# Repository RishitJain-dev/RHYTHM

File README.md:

# RHYTHM
a grid of 168 RGB LEDs to connect with hackatime or github to represent your coding time in real life, all controlled by a XIAO ESP32-S3 and LiPo battery

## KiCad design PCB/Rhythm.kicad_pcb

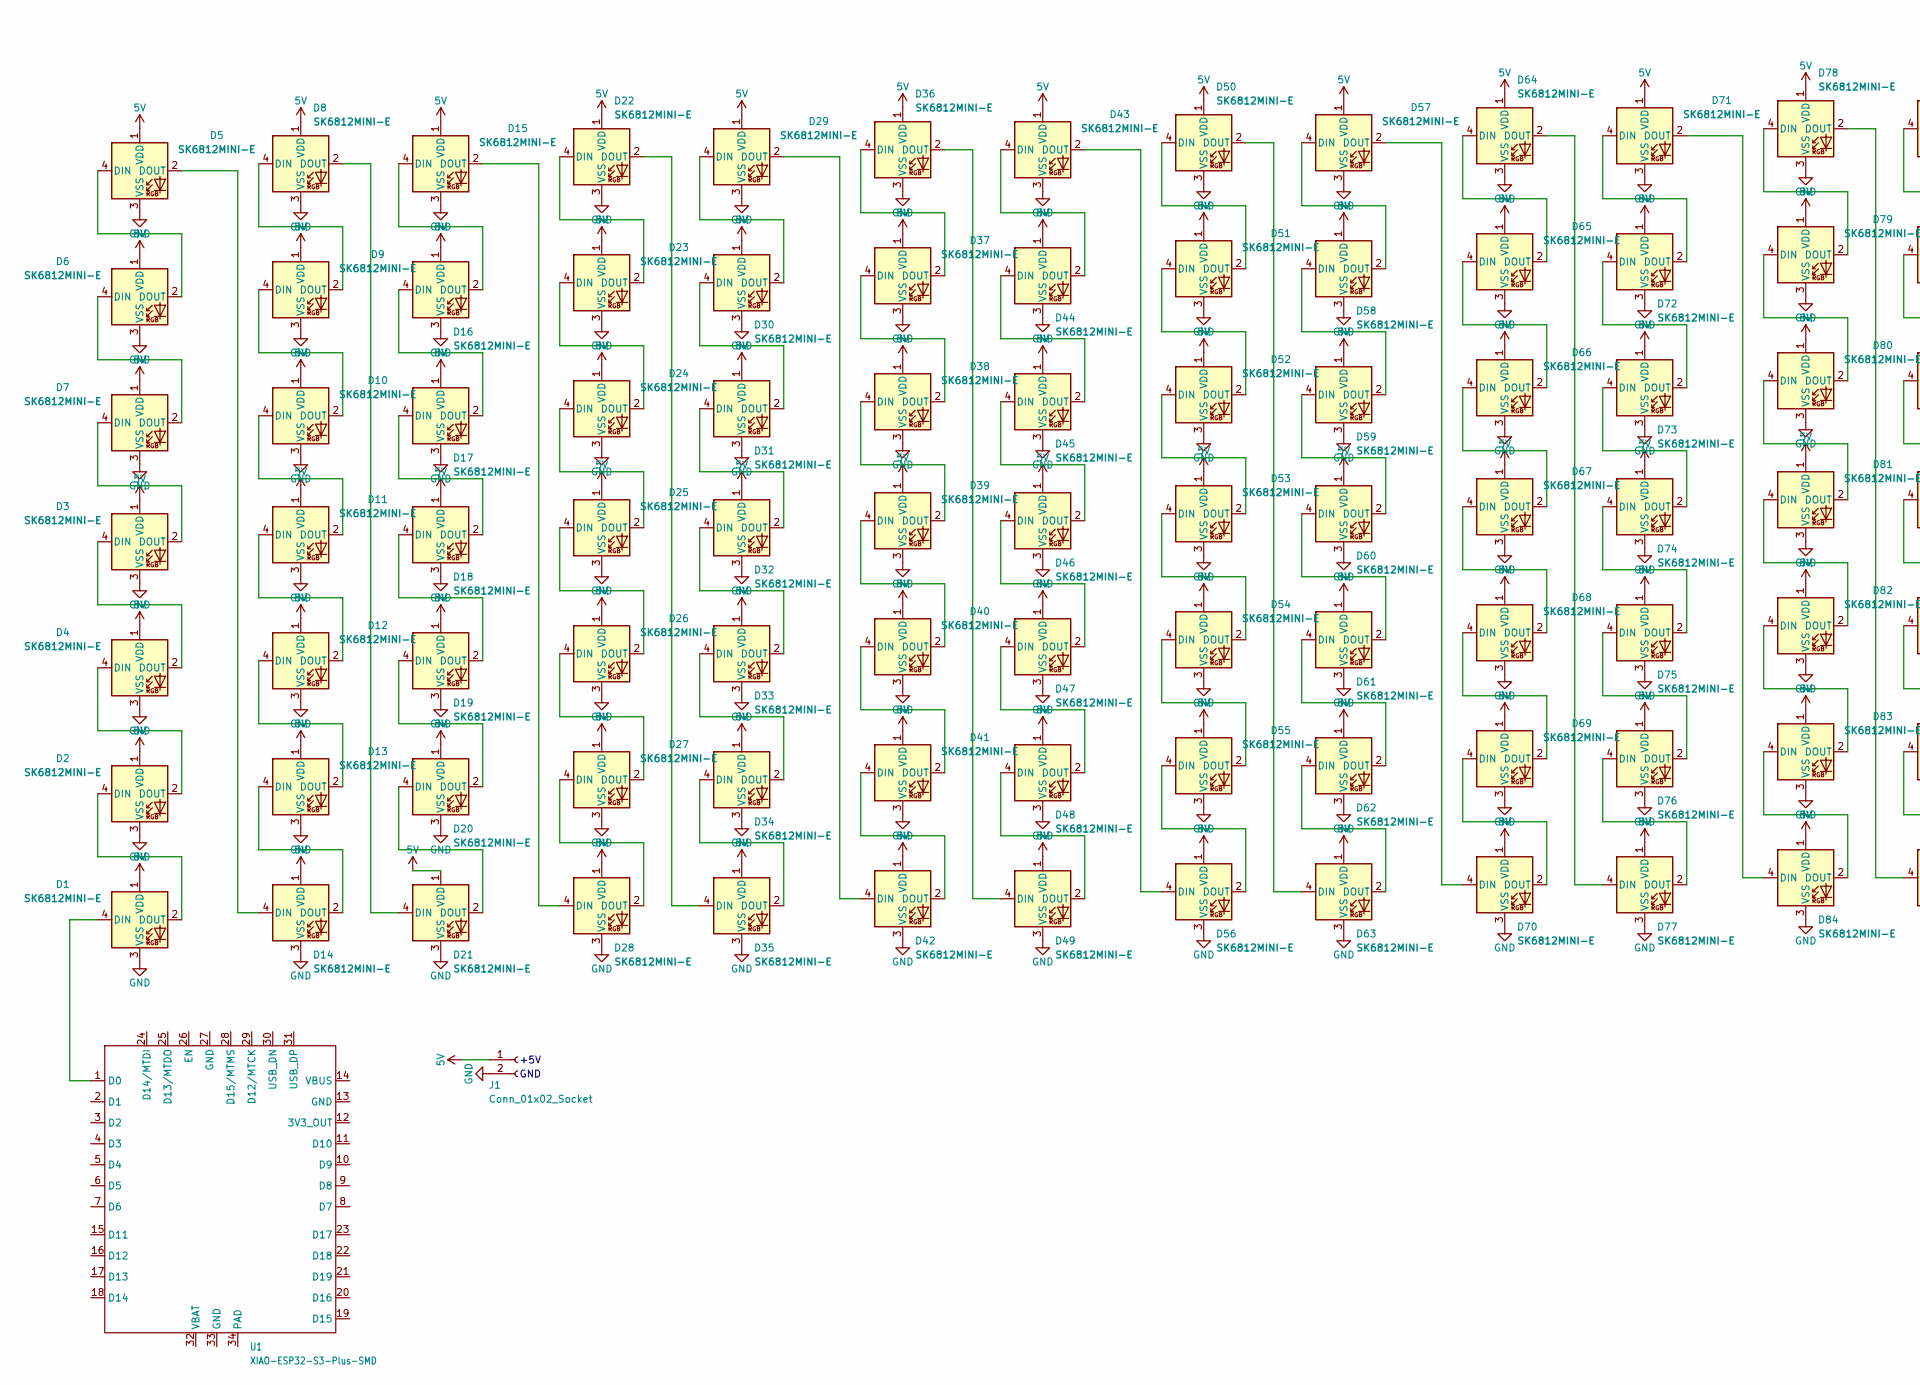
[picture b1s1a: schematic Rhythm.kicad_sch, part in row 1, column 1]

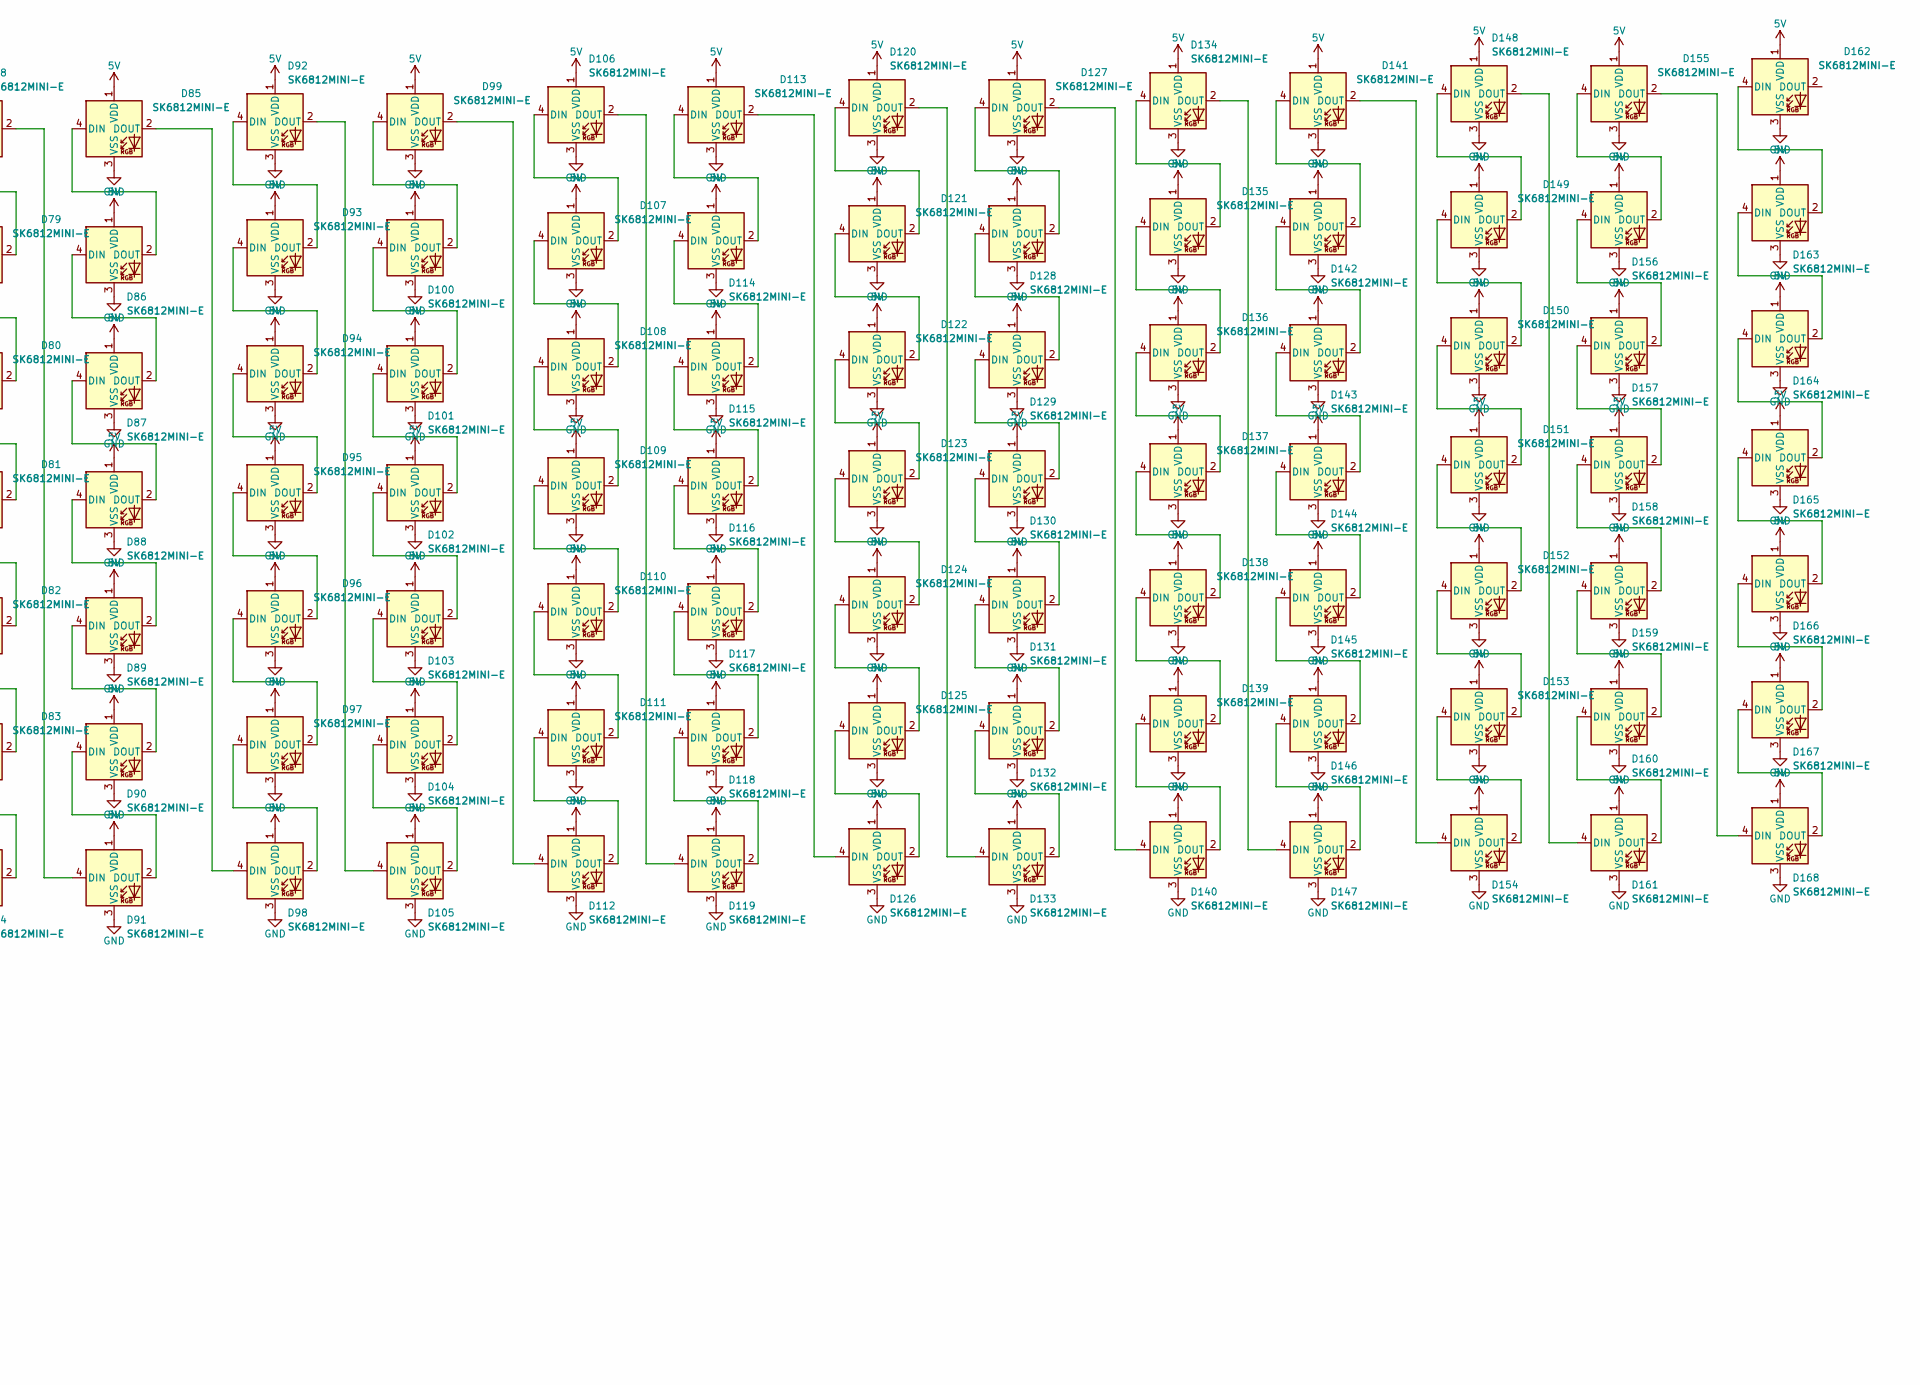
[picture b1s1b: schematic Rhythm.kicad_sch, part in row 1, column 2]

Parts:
D1, D2, D3, D4, D5, D6, D7, D8, D9, D10, D11, D12, D13, D14, D15, D16, D17, D18, D19, D20, D21, D22, D23, D24, D25, D26, D27, D28, D29, D30, D31, D32, D33, D34, D35, D36, D37, D38, D39, D40, D41, D42, D43, D44, D45, D46, D47, D48, D49, D50, D51, D52, D53, D54, D55, D56, D57, D58, D59, D60, D61, D62, D63, D64, D65, D66, D67, D68, D69, D70, D71, D72, D73, D74, D75, D76, D77, D78, D79, D80, D81, D82, D83, D84, D85, D86, D87, D88, D89, D90, D91, D92, D93, D94, D95, D96, D97, D98, D99, D100, D101, D102, D103, D104, D105, D106, D107, D108, D109, D110, D111, D112, D113, D114, D115, D116, D117, D118, D119, D120, D121, D122, D123, D124, D125, D126, D127, D128, D129, D130, D131, D132, D133, D134, D135, D136, D137, D138, D139, D140, D141, D142, D143, D144, D145, D146, D147, D148, D149, D150, D151, D152, D153, D154, D155, D156, D157, D158, D159, D160, D161, D162, D163, D164, D165, D166, D167, D168: SK6812MINI-E; SK6812MINI-E_fixed
J1: Conn_01x02_Socket; JST_EH_B2B-EH-A_1x02_P2.50mm_Vertical
U1: XIAO-ESP32-S3-Plus-SMD

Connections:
5V: D1.1 (VDD), D2.1 (VDD), D3.1 (VDD), D4.1 (VDD), D5.1 (VDD), D6.1 (VDD), D7.1 (VDD), D8.1 (VDD), D9.1 (VDD), D10.1 (VDD), D11.1 (VDD), D12.1 (VDD), D13.1 (VDD), D14.1 (VDD), D15.1 (VDD), D16.1 (VDD), D17.1 (VDD), D18.1 (VDD), D19.1 (VDD), D20.1 (VDD), D21.1 (VDD), D22.1 (VDD), D23.1 (VDD), D24.1 (VDD), D25.1 (VDD), D26.1 (VDD), D27.1 (VDD), D28.1 (VDD), D29.1 (VDD), D30.1 (VDD), D31.1 (VDD), D32.1 (VDD), D33.1 (VDD), D34.1 (VDD), D35.1 (VDD), D36.1 (VDD), D37.1 (VDD), D38.1 (VDD), D39.1 (VDD), D40.1 (VDD), D41.1 (VDD), D42.1 (VDD), D43.1 (VDD), D44.1 (VDD), D45.1 (VDD), D46.1 (VDD), D47.1 (VDD), D48.1 (VDD), D49.1 (VDD), D50.1 (VDD), D51.1 (VDD), D52.1 (VDD), D53.1 (VDD), D54.1 (VDD), D55.1 (VDD), D56.1 (VDD), D57.1 (VDD), D58.1 (VDD), D59.1 (VDD), D60.1 (VDD), D61.1 (VDD), D62.1 (VDD), D63.1 (VDD), D64.1 (VDD), D65.1 (VDD), D66.1 (VDD), D67.1 (VDD), D68.1 (VDD), D69.1 (VDD), D70.1 (VDD), D71.1 (VDD), D72.1 (VDD), D73.1 (VDD), D74.1 (VDD), D75.1 (VDD), D76.1 (VDD), D77.1 (VDD), D78.1 (VDD), D79.1 (VDD), D80.1 (VDD), D81.1 (VDD), D82.1 (VDD), D83.1 (VDD), D84.1 (VDD), D85.1 (VDD), D86.1 (VDD), D87.1 (VDD), D88.1 (VDD), D89.1 (VDD), D90.1 (VDD), D91.1 (VDD), D92.1 (VDD), D93.1 (VDD), D94.1 (VDD), D95.1 (VDD), D96.1 (VDD), D97.1 (VDD), D98.1 (VDD), D99.1 (VDD), D100.1 (VDD), D101.1 (VDD), D102.1 (VDD), D103.1 (VDD), D104.1 (VDD), D105.1 (VDD), D106.1 (VDD), D107.1 (VDD), D108.1 (VDD), D109.1 (VDD), D110.1 (VDD), D111.1 (VDD), D112.1 (VDD), D113.1 (VDD), D114.1 (VDD), D115.1 (VDD), D116.1 (VDD), D117.1 (VDD), D118.1 (VDD), D119.1 (VDD), D120.1 (VDD), D121.1 (VDD), D122.1 (VDD), D123.1 (VDD), D124.1 (VDD), D125.1 (VDD), D126.1 (VDD), D127.1 (VDD), D128.1 (VDD), D129.1 (VDD), D130.1 (VDD), D131.1 (VDD), D132.1 (VDD), D133.1 (VDD), D134.1 (VDD), D135.1 (VDD), D136.1 (VDD), D137.1 (VDD), D138.1 (VDD), D139.1 (VDD), D140.1 (VDD), D141.1 (VDD), D142.1 (VDD), D143.1 (VDD), D144.1 (VDD), D145.1 (VDD), D146.1 (VDD), D147.1 (VDD), D148.1 (VDD), D149.1 (VDD), D150.1 (VDD), D151.1 (VDD), D152.1 (VDD), D153.1 (VDD), D154.1 (VDD), D155.1 (VDD), D156.1 (VDD), D157.1 (VDD), D158.1 (VDD), D159.1 (VDD), D160.1 (VDD), D161.1 (VDD), D162.1 (VDD), D163.1 (VDD), D164.1 (VDD), D165.1 (VDD), D166.1 (VDD), D167.1 (VDD), D168.1 (VDD), J1.1
GND: D1.3 (VSS), D2.3 (VSS), D3.3 (VSS), D4.3 (VSS), D5.3 (VSS), D6.3 (VSS), D7.3 (VSS), D8.3 (VSS), D9.3 (VSS), D10.3 (VSS), D11.3 (VSS), D12.3 (VSS), D13.3 (VSS), D14.3 (VSS), D15.3 (VSS), D16.3 (VSS), D17.3 (VSS), D18.3 (VSS), D19.3 (VSS), D20.3 (VSS), D21.3 (VSS), D22.3 (VSS), D23.3 (VSS), D24.3 (VSS), D25.3 (VSS), D26.3 (VSS), D27.3 (VSS), D28.3 (VSS), D29.3 (VSS), D30.3 (VSS), D31.3 (VSS), D32.3 (VSS), D33.3 (VSS), D34.3 (VSS), D35.3 (VSS), D36.3 (VSS), D37.3 (VSS), D38.3 (VSS), D39.3 (VSS), D40.3 (VSS), D41.3 (VSS), D42.3 (VSS), D43.3 (VSS), D44.3 (VSS), D45.3 (VSS), D46.3 (VSS), D47.3 (VSS), D48.3 (VSS), D49.3 (VSS), D50.3 (VSS), D51.3 (VSS), D52.3 (VSS), D53.3 (VSS), D54.3 (VSS), D55.3 (VSS), D56.3 (VSS), D57.3 (VSS), D58.3 (VSS), D59.3 (VSS), D60.3 (VSS), D61.3 (VSS), D62.3 (VSS), D63.3 (VSS), D64.3 (VSS), D65.3 (VSS), D66.3 (VSS), D67.3 (VSS), D68.3 (VSS), D69.3 (VSS), D70.3 (VSS), D71.3 (VSS), D72.3 (VSS), D73.3 (VSS), D74.3 (VSS), D75.3 (VSS), D76.3 (VSS), D77.3 (VSS), D78.3 (VSS), D79.3 (VSS), D80.3 (VSS), D81.3 (VSS), D82.3 (VSS), D83.3 (VSS), D84.3 (VSS), D85.3 (VSS), D86.3 (VSS), D87.3 (VSS), D88.3 (VSS), D89.3 (VSS), D90.3 (VSS), D91.3 (VSS), D92.3 (VSS), D93.3 (VSS), D94.3 (VSS), D95.3 (VSS), D96.3 (VSS), D97.3 (VSS), D98.3 (VSS), D99.3 (VSS), D100.3 (VSS), D101.3 (VSS), D102.3 (VSS), D103.3 (VSS), D104.3 (VSS), D105.3 (VSS), D106.3 (VSS), D107.3 (VSS), D108.3 (VSS), D109.3 (VSS), D110.3 (VSS), D111.3 (VSS), D112.3 (VSS), D113.3 (VSS), D114.3 (VSS), D115.3 (VSS), D116.3 (VSS), D117.3 (VSS), D118.3 (VSS), D119.3 (VSS), D120.3 (VSS), D121.3 (VSS), D122.3 (VSS), D123.3 (VSS), D124.3 (VSS), D125.3 (VSS), D126.3 (VSS), D127.3 (VSS), D128.3 (VSS), D129.3 (VSS), D130.3 (VSS), D131.3 (VSS), D132.3 (VSS), D133.3 (VSS), D134.3 (VSS), D135.3 (VSS), D136.3 (VSS), D137.3 (VSS), D138.3 (VSS), D139.3 (VSS), D140.3 (VSS), D141.3 (VSS), D142.3 (VSS), D143.3 (VSS), D144.3 (VSS), D145.3 (VSS), D146.3 (VSS), D147.3 (VSS), D148.3 (VSS), D149.3 (VSS), D150.3 (VSS), D151.3 (VSS), D152.3 (VSS), D153.3 (VSS), D154.3 (VSS), D155.3 (VSS), D156.3 (VSS), D157.3 (VSS), D158.3 (VSS), D159.3 (VSS), D160.3 (VSS), D161.3 (VSS), D162.3 (VSS), D163.3 (VSS), D164.3 (VSS), D165.3 (VSS), D166.3 (VSS), D167.3 (VSS), D168.3 (VSS), J1.2
unnamed: D1.4 (DIN), U1.1 (D0_1)
unnamed: D1.2 (DOUT), D2.4 (DIN)
unnamed: D2.2 (DOUT), D4.4 (DIN)
unnamed: D3.4 (DIN), D4.2 (DOUT)
unnamed: D3.2 (DOUT), D7.4 (DIN)
unnamed: D5.4 (DIN), D6.2 (DOUT)
unnamed: D6.4 (DIN), D7.2 (DOUT)
unnamed: D8.4 (DIN), D9.2 (DOUT)
unnamed: D10.4 (DIN), D11.2 (DOUT)
unnamed: D9.4 (DIN), D10.2 (DOUT)
unnamed: D11.4 (DIN), D12.2 (DOUT)
unnamed: D12.4 (DIN), D13.2 (DOUT)
unnamed: D13.4 (DIN), D14.2 (DOUT)
unnamed: D5.2 (DOUT), D14.4 (DIN)
unnamed: D15.4 (DIN), D16.2 (DOUT)
unnamed: D15.2 (DOUT), D28.4 (DIN)
unnamed: D16.4 (DIN), D17.2 (DOUT)
unnamed: D17.4 (DIN), D18.2 (DOUT)
unnamed: D18.4 (DIN), D19.2 (DOUT)
unnamed: D19.4 (DIN), D20.2 (DOUT)
unnamed: D20.4 (DIN), D21.2 (DOUT)
unnamed: D8.2 (DOUT), D21.4 (DIN)
unnamed: D22.4 (DIN), D23.2 (DOUT)
unnamed: D22.2 (DOUT), D35.4 (DIN)
unnamed: D23.4 (DIN), D24.2 (DOUT)
unnamed: D24.4 (DIN), D25.2 (DOUT)
unnamed: D25.4 (DIN), D26.2 (DOUT)
unnamed: D26.4 (DIN), D27.2 (DOUT)
unnamed: D27.4 (DIN), D28.2 (DOUT)
unnamed: D29.4 (DIN), D30.2 (DOUT)
unnamed: D29.2 (DOUT), D42.4 (DIN)
unnamed: D30.4 (DIN), D31.2 (DOUT)
unnamed: D31.4 (DIN), D32.2 (DOUT)
unnamed: D32.4 (DIN), D33.2 (DOUT)
unnamed: D33.4 (DIN), D34.2 (DOUT)
unnamed: D34.4 (DIN), D35.2 (DOUT)
unnamed: D36.4 (DIN), D37.2 (DOUT)
unnamed: D36.2 (DOUT), D49.4 (DIN)
unnamed: D37.4 (DIN), D38.2 (DOUT)
unnamed: D38.4 (DIN), D39.2 (DOUT)
unnamed: D39.4 (DIN), D40.2 (DOUT)
unnamed: D40.4 (DIN), D41.2 (DOUT)
unnamed: D41.4 (DIN), D42.2 (DOUT)
unnamed: D43.4 (DIN), D44.2 (DOUT)
unnamed: D43.2 (DOUT), D56.4 (DIN)
unnamed: D44.4 (DIN), D45.2 (DOUT)
unnamed: D45.4 (DIN), D46.2 (DOUT)
unnamed: D46.4 (DIN), D47.2 (DOUT)
unnamed: D47.4 (DIN), D48.2 (DOUT)
unnamed: D48.4 (DIN), D49.2 (DOUT)
unnamed: D50.4 (DIN), D51.2 (DOUT)
unnamed: D50.2 (DOUT), D63.4 (DIN)
unnamed: D51.4 (DIN), D52.2 (DOUT)
unnamed: D52.4 (DIN), D53.2 (DOUT)
unnamed: D53.4 (DIN), D54.2 (DOUT)
unnamed: D54.4 (DIN), D55.2 (DOUT)
unnamed: D55.4 (DIN), D56.2 (DOUT)
unnamed: D57.4 (DIN), D58.2 (DOUT)
unnamed: D57.2 (DOUT), D70.4 (DIN)
unnamed: D58.4 (DIN), D59.2 (DOUT)
unnamed: D59.4 (DIN), D60.2 (DOUT)
unnamed: D60.4 (DIN), D61.2 (DOUT)
unnamed: D61.4 (DIN), D62.2 (DOUT)
unnamed: D62.4 (DIN), D63.2 (DOUT)
unnamed: D64.4 (DIN), D65.2 (DOUT)
unnamed: D64.2 (DOUT), D77.4 (DIN)
unnamed: D65.4 (DIN), D66.2 (DOUT)
unnamed: D66.4 (DIN), D67.2 (DOUT)
unnamed: D67.4 (DIN), D68.2 (DOUT)
unnamed: D68.4 (DIN), D69.2 (DOUT)
unnamed: D69.4 (DIN), D70.2 (DOUT)
unnamed: D71.4 (DIN), D72.2 (DOUT)
unnamed: D71.2 (DOUT), D84.4 (DIN)
unnamed: D72.4 (DIN), D73.2 (DOUT)
unnamed: D73.4 (DIN), D74.2 (DOUT)
unnamed: D74.4 (DIN), D75.2 (DOUT)
unnamed: D75.4 (DIN), D76.2 (DOUT)
unnamed: D76.4 (DIN), D77.2 (DOUT)
unnamed: D78.4 (DIN), D79.2 (DOUT)
unnamed: D78.2 (DOUT), D91.4 (DIN)
unnamed: D79.4 (DIN), D80.2 (DOUT)
unnamed: D80.4 (DIN), D81.2 (DOUT)
unnamed: D81.4 (DIN), D82.2 (DOUT)
unnamed: D82.4 (DIN), D83.2 (DOUT)
unnamed: D83.4 (DIN), D84.2 (DOUT)
unnamed: D85.4 (DIN), D86.2 (DOUT)
unnamed: D85.2 (DOUT), D98.4 (DIN)
unnamed: D86.4 (DIN), D87.2 (DOUT)
unnamed: D87.4 (DIN), D88.2 (DOUT)
unnamed: D88.4 (DIN), D89.2 (DOUT)
unnamed: D89.4 (DIN), D90.2 (DOUT)
unnamed: D90.4 (DIN), D91.2 (DOUT)
unnamed: D92.4 (DIN), D93.2 (DOUT)
unnamed: D93.4 (DIN), D94.2 (DOUT)
unnamed: D94.4 (DIN), D95.2 (DOUT)
unnamed: D95.4 (DIN), D96.2 (DOUT)
unnamed: D96.4 (DIN), D97.2 (DOUT)
unnamed: D97.4 (DIN), D98.2 (DOUT)
unnamed: D100.4 (DIN), D101.2 (DOUT)
unnamed: D99.4 (DIN), D100.2 (DOUT)
unnamed: D101.4 (DIN), D102.2 (DOUT)
unnamed: D102.4 (DIN), D103.2 (DOUT)
unnamed: D103.4 (DIN), D104.2 (DOUT)
unnamed: D104.4 (DIN), D105.2 (DOUT)
unnamed: D92.2 (DOUT), D105.4 (DIN)
unnamed: D106.4 (DIN), D107.2 (DOUT)
unnamed: D106.2 (DOUT), D119.4 (DIN)
unnamed: D107.4 (DIN), D108.2 (DOUT)
unnamed: D108.4 (DIN), D109.2 (DOUT)
unnamed: D109.4 (DIN), D110.2 (DOUT)
unnamed: D110.4 (DIN), D111.2 (DOUT)
unnamed: D111.4 (DIN), D112.2 (DOUT)
unnamed: D99.2 (DOUT), D112.4 (DIN)
unnamed: D113.4 (DIN), D114.2 (DOUT)
unnamed: D113.2 (DOUT), D126.4 (DIN)
unnamed: D114.4 (DIN), D115.2 (DOUT)
unnamed: D115.4 (DIN), D116.2 (DOUT)
unnamed: D116.4 (DIN), D117.2 (DOUT)
unnamed: D117.4 (DIN), D118.2 (DOUT)
unnamed: D118.4 (DIN), D119.2 (DOUT)
unnamed: D120.4 (DIN), D121.2 (DOUT)
unnamed: D120.2 (DOUT), D133.4 (DIN)
unnamed: D121.4 (DIN), D122.2 (DOUT)
unnamed: D122.4 (DIN), D123.2 (DOUT)
unnamed: D123.4 (DIN), D124.2 (DOUT)
unnamed: D124.4 (DIN), D125.2 (DOUT)
unnamed: D125.4 (DIN), D126.2 (DOUT)
unnamed: D127.4 (DIN), D128.2 (DOUT)
unnamed: D127.2 (DOUT), D140.4 (DIN)
unnamed: D128.4 (DIN), D129.2 (DOUT)
unnamed: D129.4 (DIN), D130.2 (DOUT)
unnamed: D130.4 (DIN), D131.2 (DOUT)
unnamed: D131.4 (DIN), D132.2 (DOUT)
unnamed: D132.4 (DIN), D133.2 (DOUT)
unnamed: D134.4 (DIN), D135.2 (DOUT)
unnamed: D134.2 (DOUT), D147.4 (DIN)
unnamed: D135.4 (DIN), D136.2 (DOUT)
unnamed: D136.4 (DIN), D137.2 (DOUT)
unnamed: D137.4 (DIN), D138.2 (DOUT)
unnamed: D138.4 (DIN), D139.2 (DOUT)
unnamed: D139.4 (DIN), D140.2 (DOUT)
unnamed: D141.4 (DIN), D142.2 (DOUT)
unnamed: D141.2 (DOUT), D154.4 (DIN)
unnamed: D142.4 (DIN), D143.2 (DOUT)
unnamed: D143.4 (DIN), D144.2 (DOUT)
unnamed: D144.4 (DIN), D145.2 (DOUT)
unnamed: D145.4 (DIN), D146.2 (DOUT)
unnamed: D146.4 (DIN), D147.2 (DOUT)
unnamed: D148.4 (DIN), D149.2 (DOUT)
unnamed: D148.2 (DOUT), D161.4 (DIN)
unnamed: D149.4 (DIN), D150.2 (DOUT)
unnamed: D150.4 (DIN), D151.2 (DOUT)
unnamed: D151.4 (DIN), D152.2 (DOUT)
unnamed: D152.4 (DIN), D153.2 (DOUT)
unnamed: D153.4 (DIN), D154.2 (DOUT)
unnamed: D155.4 (DIN), D156.2 (DOUT)
unnamed: D155.2 (DOUT), D168.4 (DIN)
unnamed: D156.4 (DIN), D157.2 (DOUT)
unnamed: D157.4 (DIN), D158.2 (DOUT)
unnamed: D158.4 (DIN), D159.2 (DOUT)
unnamed: D159.4 (DIN), D160.2 (DOUT)
unnamed: D160.4 (DIN), D161.2 (DOUT)
unnamed: D162.4 (DIN), D163.2 (DOUT)
unnamed: D163.4 (DIN), D164.2 (DOUT)
unnamed: D164.4 (DIN), D165.2 (DOUT)
unnamed: D165.4 (DIN), D166.2 (DOUT)
unnamed: D166.4 (DIN), D167.2 (DOUT)
unnamed: D167.4 (DIN), D168.2 (DOUT)

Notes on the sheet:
GND
+5V

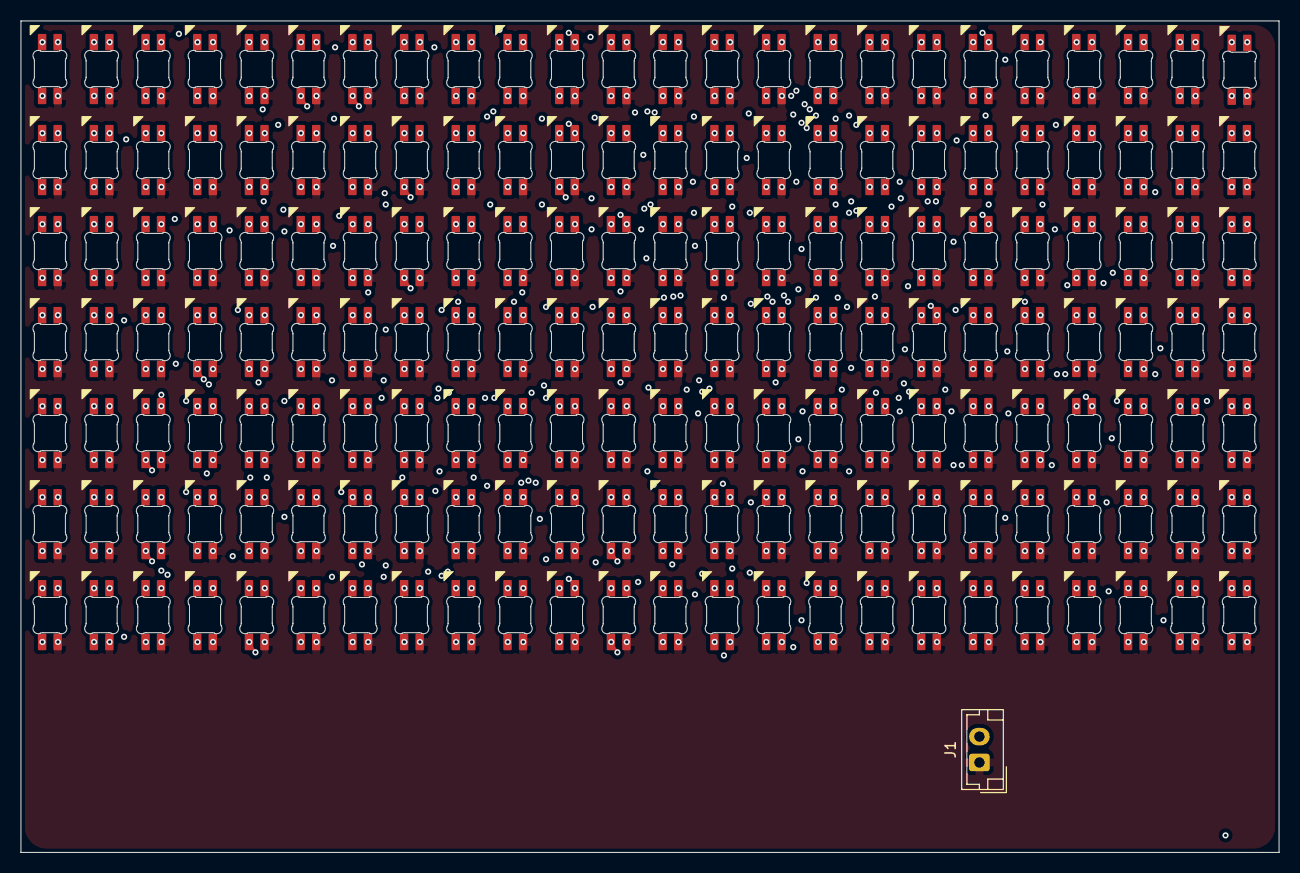
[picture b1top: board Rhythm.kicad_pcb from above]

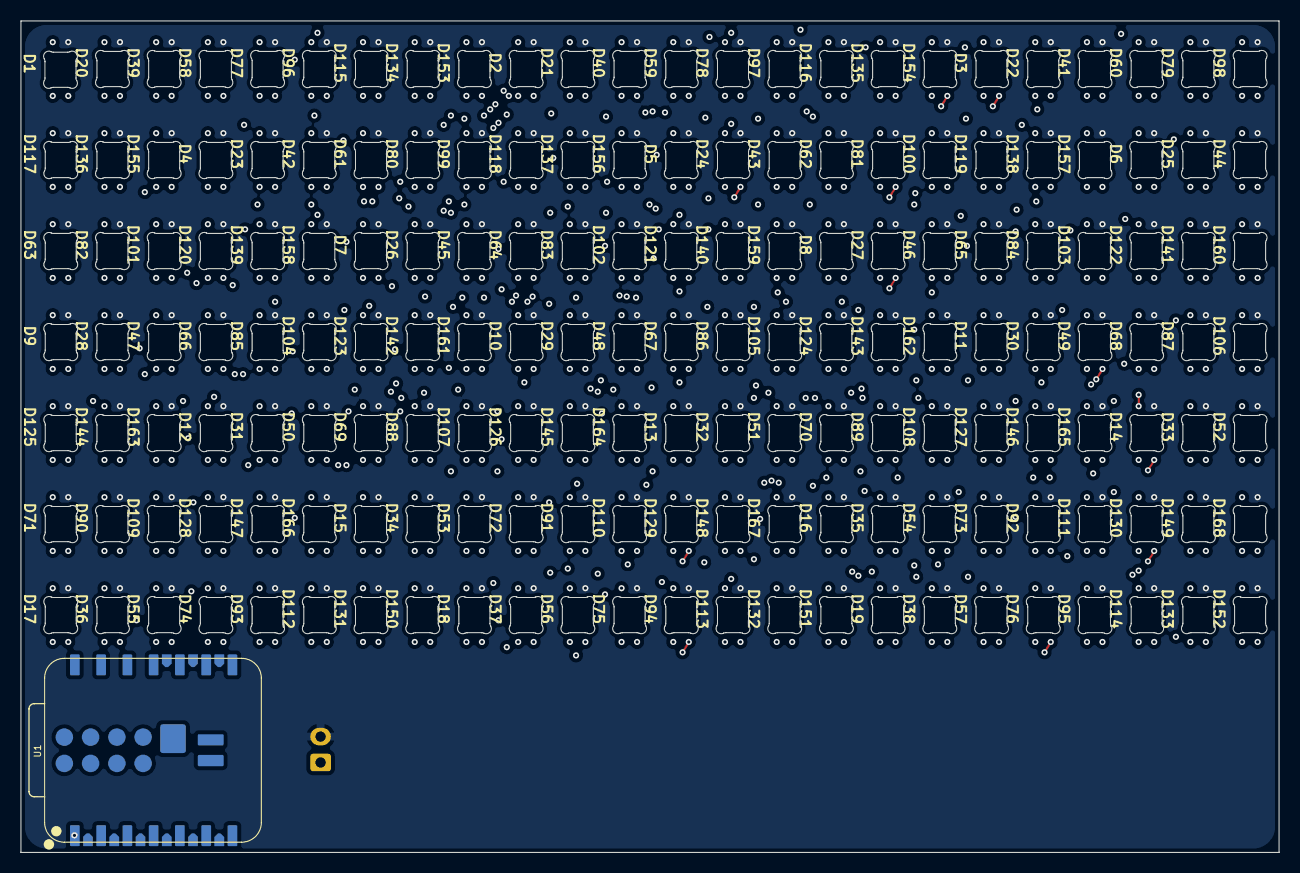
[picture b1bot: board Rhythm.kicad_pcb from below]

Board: 8 copper layers, 121.7 x 80.4 mm, 170 parts (169 on the bottom side), 170 nets.
